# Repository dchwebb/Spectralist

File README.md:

# Spectralist

## Overview

Spectralist is an additive oscillator for Eurorack modular synthesisers. Up to 300 harmonics are output over two separate Odd and Even channels with a 'filter' offering a range of options for sculpting the harmonic spectrum of the output signals.

There are two harmonic modes - individual harmonics and sinusoidal waves of harmonics. In individual harmonic mode the spread controls adjust the spacing of the harmonics and the warp control either progressively bunches up or spreads out the harmonics. In the sinusoidal mode the spread controls increase the frequency of the 'waves' of harmonics.

The filter can be selected as a low pass filter with continuously adjustable slope or as a comb filter with adjustable tooth width and spread. In the comb filter mode the channel filter controls set the width between teeth and the slope sets the rise and fall times of the teeth. The individual channel filters controls can be adjusted with potentiometers or by CV with with trimmers to attenuate.

The pan CV input allows each channel to be smoothly panned between the two outputs. This can be used to mix the signals together in a mono setup, or used to dynamically shift the harmonics in the stereo field.

In the centre of the module is a ring of LEDs that give a visual representation of the harmonic spread and warp settings.

The module was designed in conjunction with musician Tal Shoshani who produced the following demonstration video:

## Technical

The module is based around an STM32H723VGT microcontroller, clocked at 400MHz. A TI PCM5100APW 32 bit audio DAC is used for the two channel outputs.

A TL072 dual op-amps is used to amplify and filter the DAC output (and/or phase invert) the outputs from 3V to 9V peak-to-peak at maximum. Input CV signals are conditioned by MCP6004 op-amps.

A USB B micro port is available at the rear of the unit for software updgrades and configuration via a serial connection.

The animated 25 LED display is driven over I2C by a PCA9956B LED Driver and the SMD LEDs sit on a daughter board raising them to the level of the front panel.

[Components schematic](Hardware/Spectralist_Components.pdf)

[LED daughterboard schematic](Hardware/Spectralist_LED_Daughterboard.pdf)

[Controls schematic](Hardware/Spectralist_Controls.pdf)

## Power

Analog power is supplied via a 3.3V LDO regulator and digital power uses a TPS561201 switching power supply.

- +12V current draw: 139 mA
- -12V Current draw: 7 mA

## Errata

Panel Errata: Mode switch hole too large for subminiature switch
Filter type switch hole just too narrow
Harm_Warp_pot and Harm_Stretch_Pot wrong way round (fixed 1.1)

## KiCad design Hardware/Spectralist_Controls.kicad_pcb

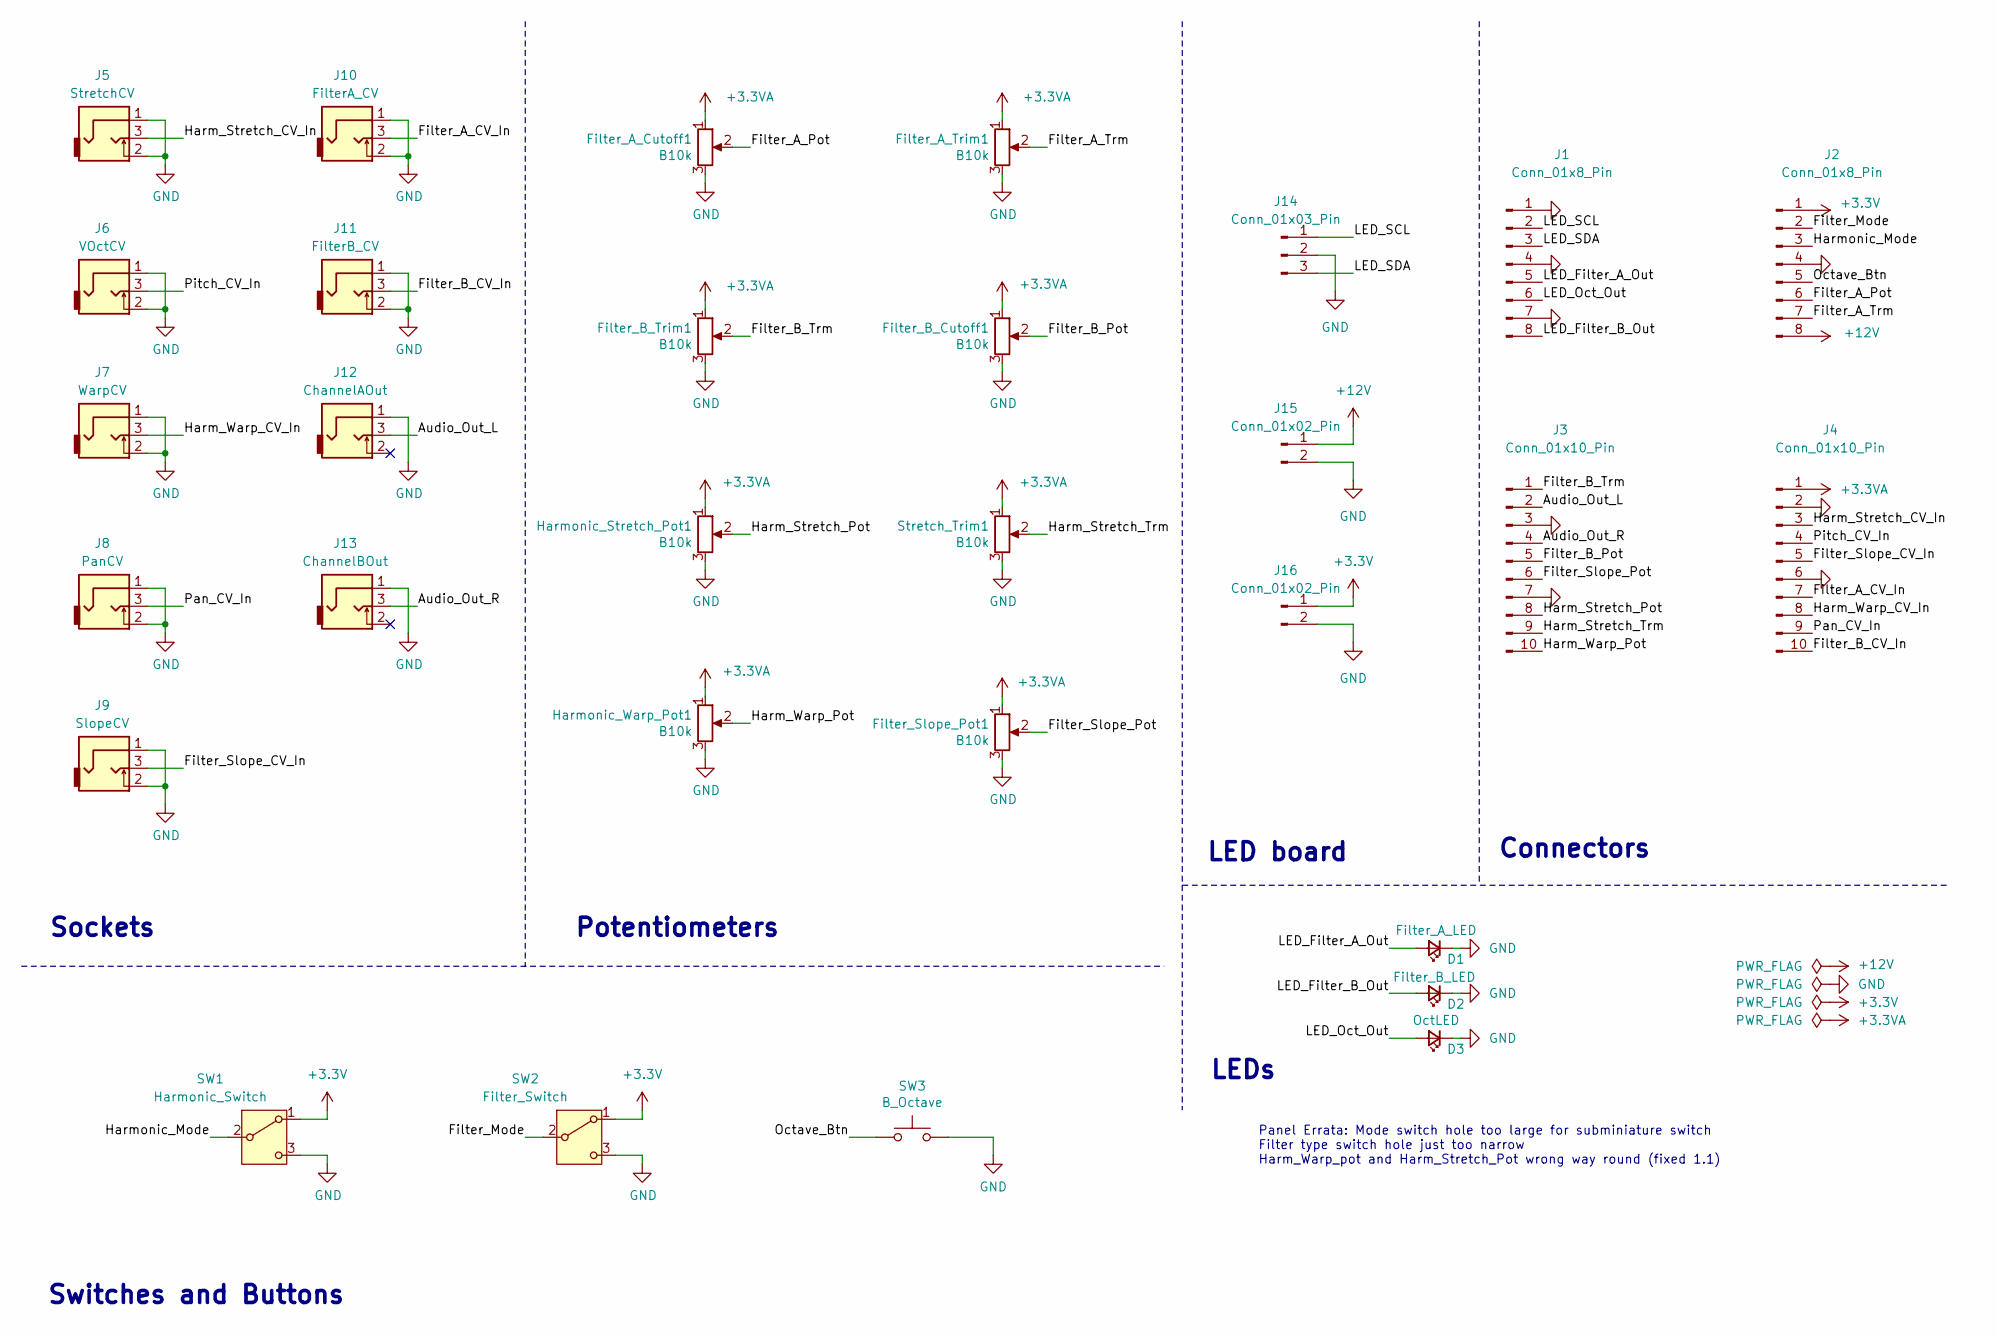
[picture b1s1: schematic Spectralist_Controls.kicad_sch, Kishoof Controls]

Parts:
D1: Filter_A_LED; LED_D3.0mm
D2: Filter_B_LED; LED_D3.0mm
D3: OctLED; LED_D3.0mm
Filter_A_Cutoff1: B10k; Alpha_9mm_Potentiometer_Aligned
Filter_A_Trim1: B10k; Alpha_9mm_Potentiometer_Aligned
Filter_B_Cutoff1: B10k; Alpha_9mm_Potentiometer_Aligned
Filter_B_Trim1: B10k; Alpha_9mm_Potentiometer_Aligned
Filter_Slope_Pot1: B10k; Alpha_9mm_Potentiometer_Aligned
Harmonic_Stretch_Pot1: B10k; Alpha_9mm_Potentiometer_Aligned
Harmonic_Warp_Pot1: B10k; Alpha_9mm_Potentiometer_Aligned
J1, J2: Conn_01x8_Pin; PinSocket_1x08_P2.54mm_Vertical
J3, J4: Conn_01x10_Pin; PinSocket_1x10_P2.54mm_Vertical
J5: StretchCV; THONKICONN_hole
J6: VOctCV; THONKICONN_hole
J7: WarpCV; THONKICONN_hole
J8: PanCV; THONKICONN_hole
J9: SlopeCV; THONKICONN_hole
J10: FilterA_CV; THONKICONN_hole
J11: FilterB_CV; THONKICONN_hole
J12: ChannelAOut; THONKICONN_hole
J13: ChannelBOut; THONKICONN_hole
J14: Conn_01x03_Pin; PinHeader_1x03_P2.54mm_Vertical
J15, J16: Conn_01x02_Pin; PinHeader_1x02_P2.54mm_Vertical
SW1: Harmonic_Switch; SPDT_SubMiniature_Aligned
SW2: Filter_Switch; SPDT_Miniature
SW3: B_Octave; SW_PUSH_6mm_aligned
Stretch_Trim1: B10k; Alpha_9mm_Potentiometer_Aligned

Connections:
+3.3V: J2.1, J16.1, SW1.1 (A), SW2.1 (A)
+3.3VA: Filter_A_Cutoff1.1, Filter_A_Trim1.1, Filter_B_Cutoff1.1, Filter_B_Trim1.1, Filter_Slope_Pot1.1, Harmonic_Stretch_Pot1.1, Harmonic_Warp_Pot1.1, J4.1, Stretch_Trim1.1
+12V: J2.8, J15.1
/Audio_Out_L: J3.2, J12.3
/Audio_Out_R: J3.4, J13.3
/Filter_A_CV_In: J4.7, J10.3
/Filter_A_Pot: Filter_A_Cutoff1.2, J2.6
/Filter_A_Trm: Filter_A_Trim1.2, J2.7
/Filter_B_CV_In: J4.10, J11.3
/Filter_B_Pot: Filter_B_Cutoff1.2, J3.5
/Filter_B_Trm: Filter_B_Trim1.2, J3.1
/Filter_Mode: J2.2, SW2.2 (B)
/Filter_Slope_CV_In: J4.5, J9.3
/Filter_Slope_Pot: Filter_Slope_Pot1.2, J3.6
/Harm_Stretch_CV_In: J4.3, J5.3
/Harm_Stretch_Pot: Harmonic_Stretch_Pot1.2, J3.8
/Harm_Stretch_Trm: J3.9, Stretch_Trim1.2
/Harm_Warp_CV_In: J4.8, J7.3
/Harm_Warp_Pot: Harmonic_Warp_Pot1.2, J3.10
/Harmonic_Mode: J2.3, SW1.2 (B)
/LED_Filter_A_Out: D1.2 (A), J1.5
/LED_Filter_B_Out: D2.2 (A), J1.8
/LED_Oct_Out: D3.2 (A), J1.6
/LED_SCL: J1.2, J14.1
/LED_SDA: J1.3, J14.3
/Octave_Btn: J2.5, SW3.1
/Pan_CV_In: J4.9, J8.3
/Pitch_CV_In: J4.4, J6.3
GND: D1.1 (K), D2.1 (K), D3.1 (K), Filter_A_Cutoff1.3, Filter_A_Trim1.3, Filter_B_Cutoff1.3, Filter_B_Trim1.3, Filter_Slope_Pot1.3, Harmonic_Stretch_Pot1.3, Harmonic_Warp_Pot1.3, J1.1, J1.4, J1.7, J2.4, J3.3, J3.7, J4.2, J4.6, J5.1, J5.2, J6.1, J6.2, J7.1, J7.2, J8.1, J8.2, J9.1, J9.2, J10.1, J10.2, J11.1, J11.2, J12.1, J13.1, J14.2, J15.2, J16.2, SW1.3 (C), SW2.3 (C), SW3.2, Stretch_Trim1.3

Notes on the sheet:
Sockets
Switches and Buttons
Panel Errata: Mode switch hole too large for subminiature switch Filter type switch hole just too narrow Harm_Warp_pot and Harm_Stretch_Pot wrong way round (fixed 1.1)
Connectors
LED board
LEDs
Potentiometers

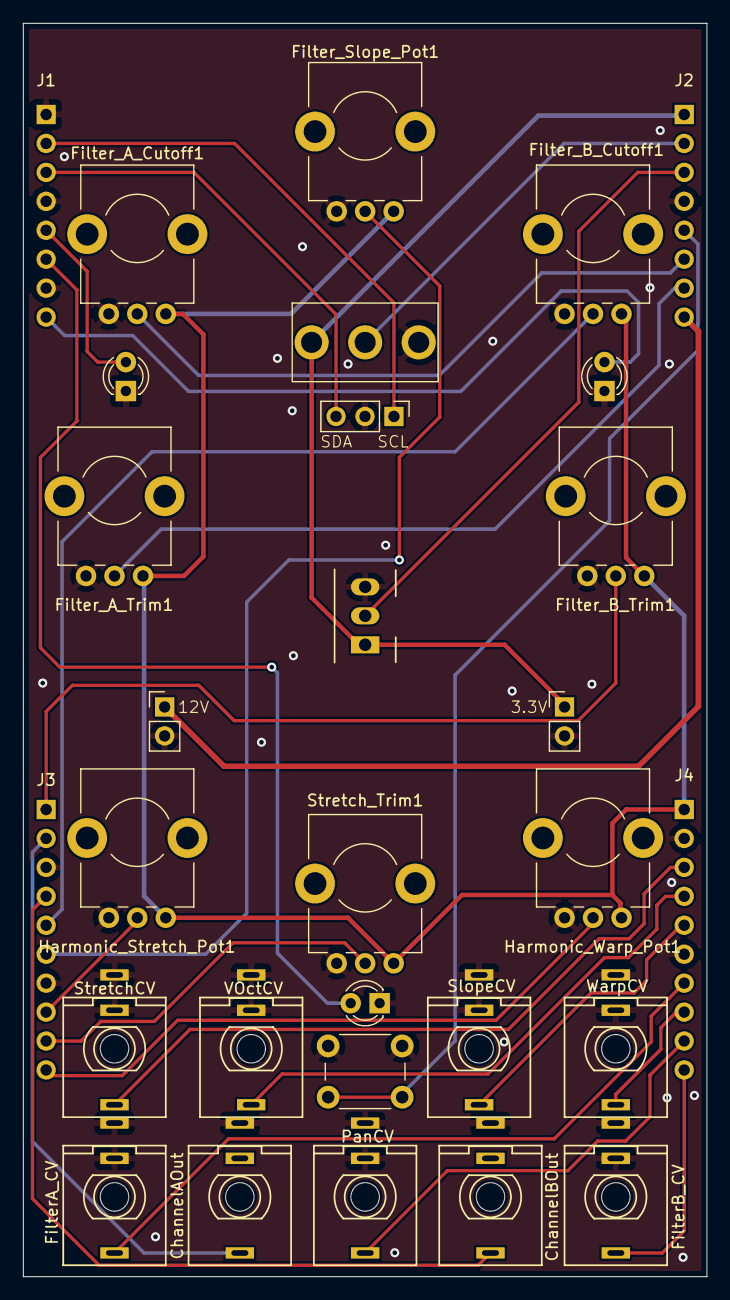
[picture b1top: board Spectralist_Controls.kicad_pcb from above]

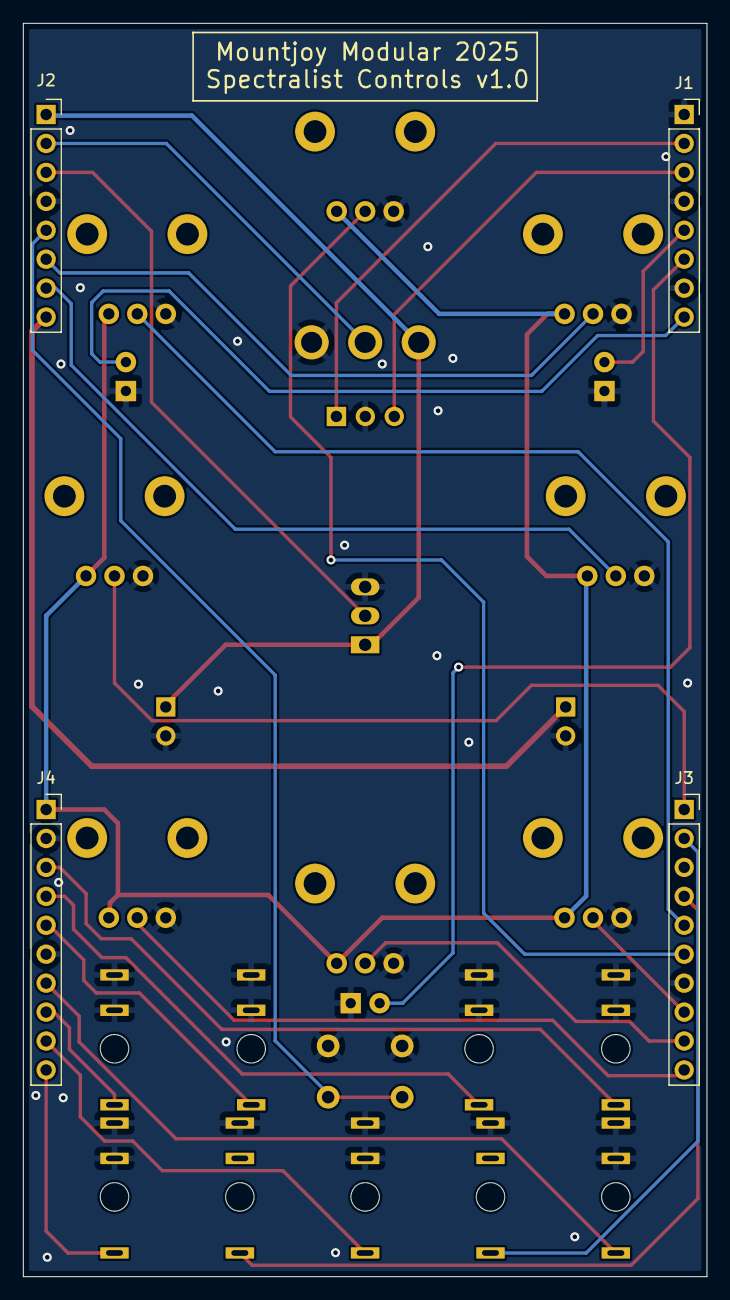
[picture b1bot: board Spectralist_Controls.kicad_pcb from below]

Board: 2 copper layers, 60.0 x 110.0 mm, 30 parts (4 on the bottom side), 29 nets.

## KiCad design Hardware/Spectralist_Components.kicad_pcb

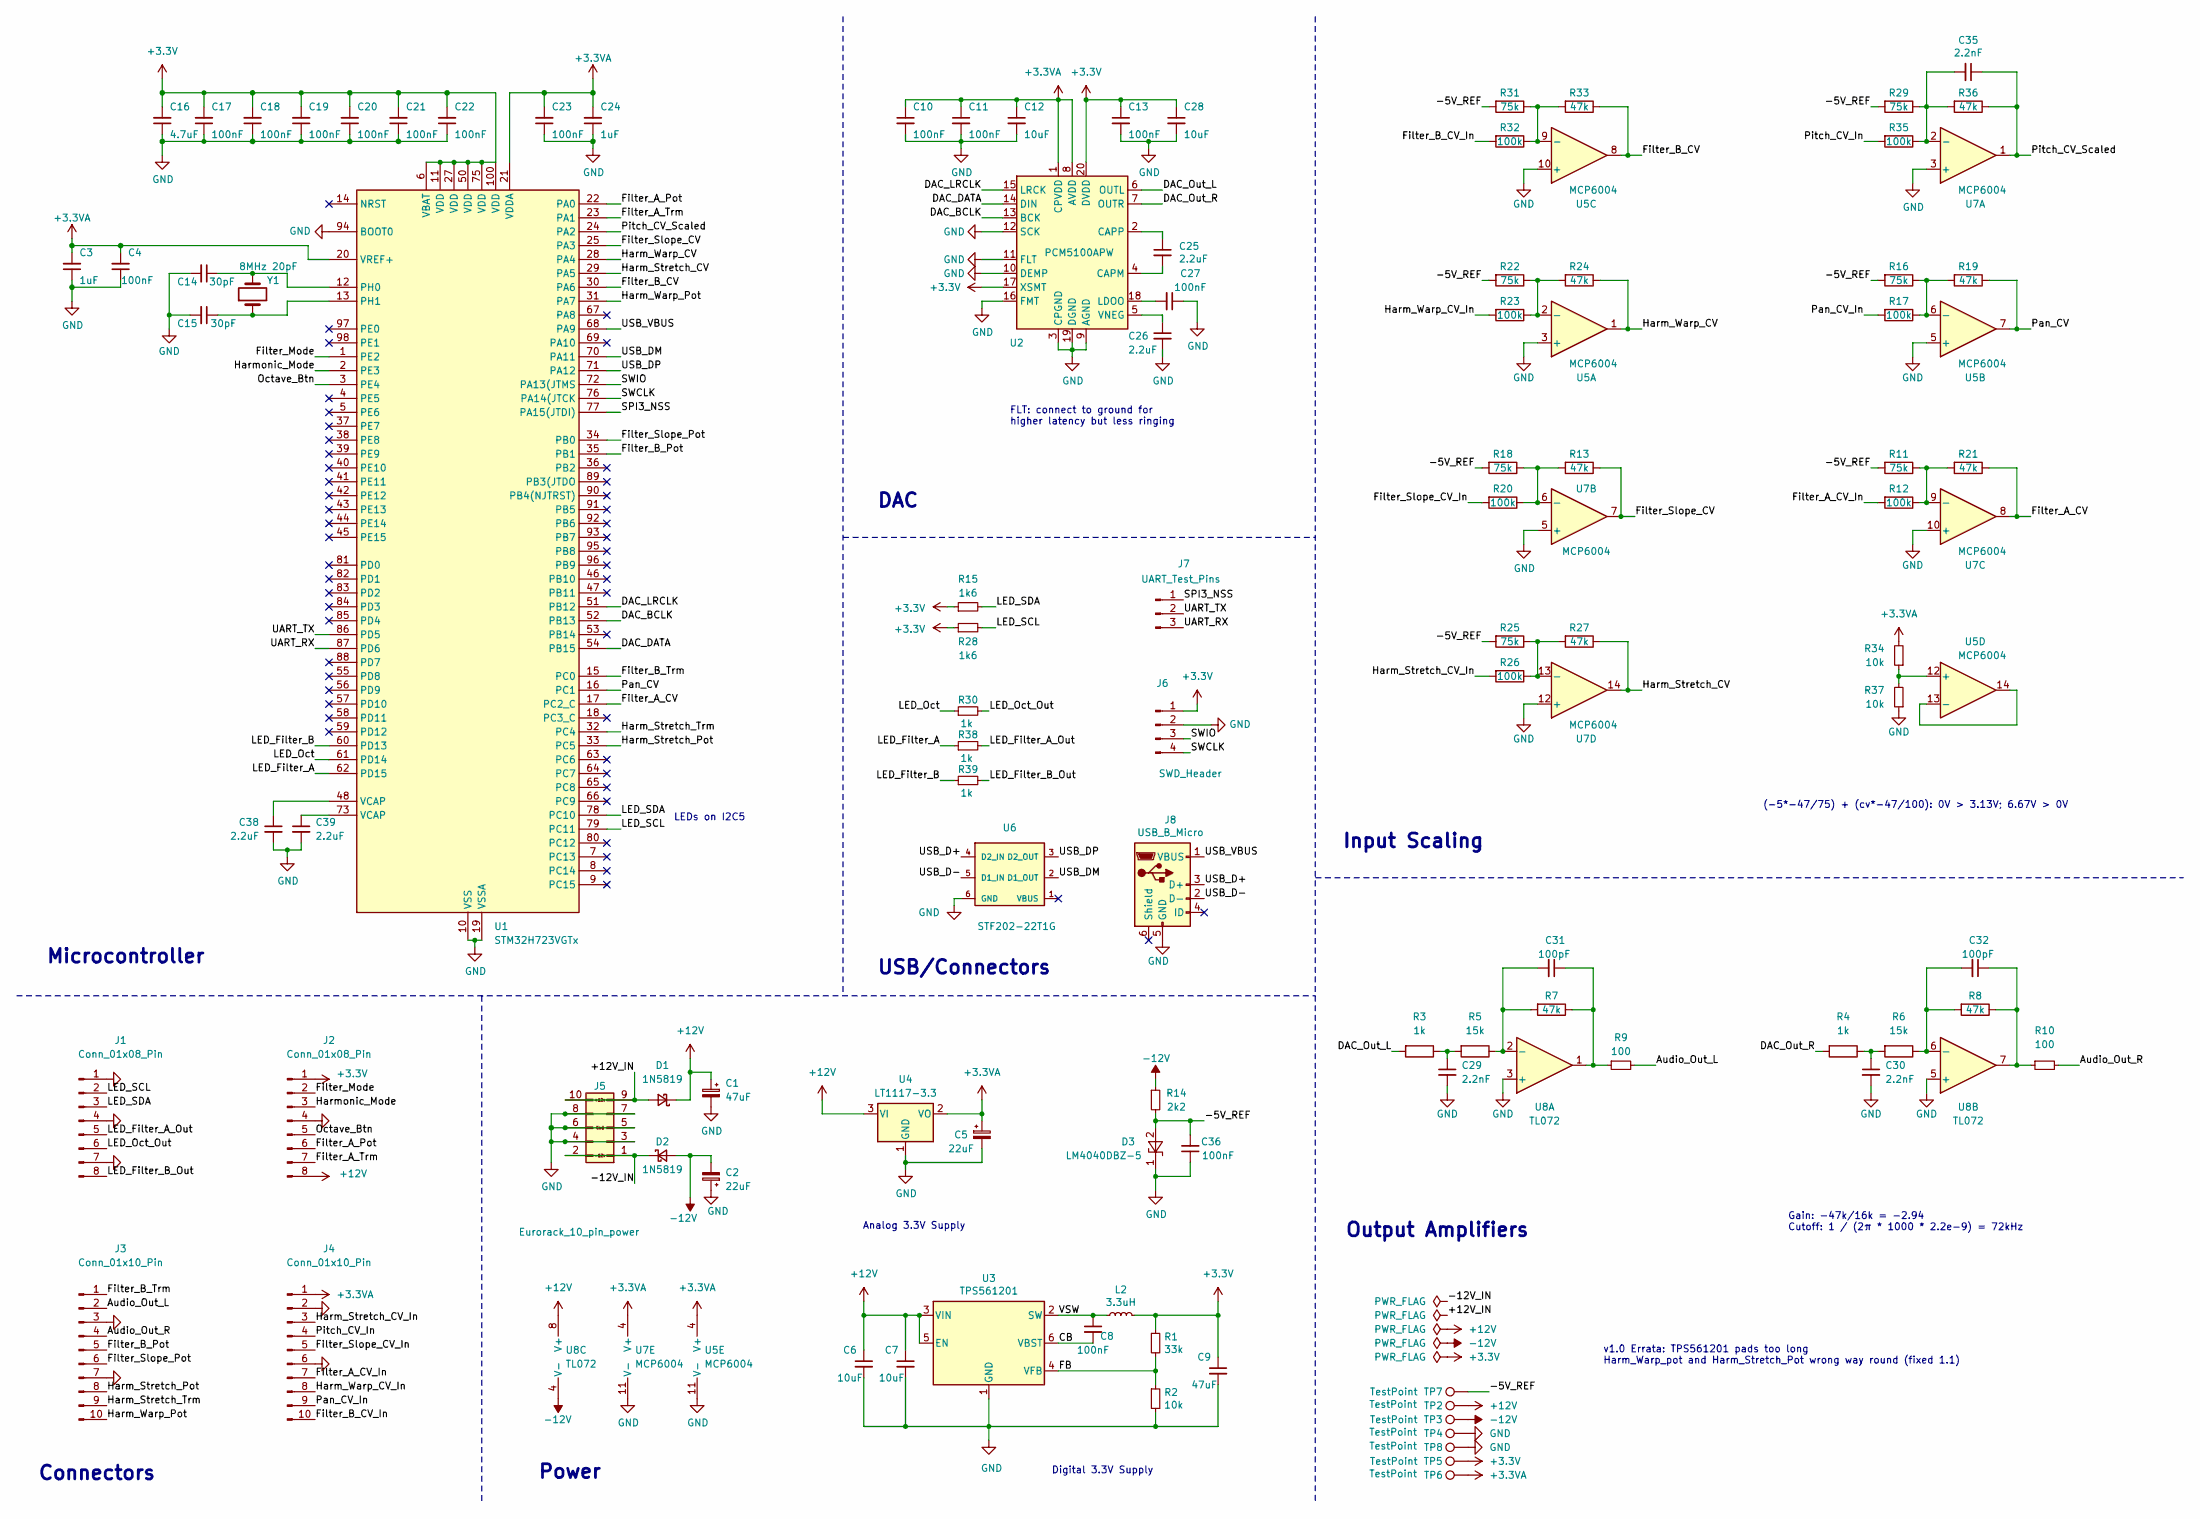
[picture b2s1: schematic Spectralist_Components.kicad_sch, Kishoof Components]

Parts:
C1: 47uF; CP_Elec_4x5.8
C2: 22uF; CP_Elec_4x5.8
C3, C24: 1uF; C_0603_1608Metric; Part_Number C15849
C4, C8, C10, C11, C13, C17, C18, C19, C20, C21, C22, C27, C36: 100nF; C_0603_1608Metric; Part_Number C14663
C5: 22uF; CP_Elec_4x5.8; Part_Number C134793
C6, C7: 10uF; C_0805_2012Metric; Part_Number C57112
C9: 47uF; C_1206_3216Metric; Part_Number C57112
C12, C28: 10uF; C_0603_1608Metric; Part_Number C15850
C14, C15: 30pF; C_0603_1608Metric; Part_Number C22397
C16: 4.7uF; C_0603_1608Metric; Part_Number C19666
C23: 100nF; C_0603_1608Metric; Part_Number C57112
C25, C26, C38, C39: 2.2uF; C_0603_1608Metric; Part_Number C23630
C29, C30, C35: 2.2nF; C_0603_1608Metric; Part_Number C1604
C31, C32: 100pF; C_0603_1608Metric; Part_Number C14858
D1, D2: 1N5819; D_SOD-123; Part_Number C8598
D3: LM4040DBZ-5; SOT-23; Part_Number C156291
J1, J2: Conn_01x08_Pin; PinHeader_1x08_P2.54mm_Vertical
J3, J4: Conn_01x10_Pin; PinHeader_1x10_P2.54mm_Vertical
J5: Eurorack_10_pin_power; Eurorack_10_pin_header
J6: SWD_Header; SWD_header
J7: UART_Test_Pins; PinHeader_1x03_P2.54mm_Vertical
J8: USB_B_Micro; USB_Micro-B_Amphenol
L2: 3.3uH; L_0806
R1: 33k; R_0603_1608Metric; Part_Number C25819
R2: 10k; R_0603_1608Metric; Part_Number C25804
R3, R4, R30, R38, R39: 1k; R_0603_1608Metric; Part_Number C4190
R5, R6: 15k; R_0603_1608Metric; Part_Number C25804
R7, R8, R13, R19, R21, R24, R27, R33, R36: 47k; R_0603_1608Metric; Part_Number C25819
R9, R10: 100; R_0603_1608Metric; Part_Number C4190
R11, R16, R18, R22, R25, R29, R31: 75k; R_0603_1608Metric; Part_Number C23242
R12, R17, R20, R23, R26, R32, R35: 100k; R_0603_1608Metric; Part_Number C23265
R14: 2k2; R_0603_1608Metric; Part_Number C4190
R15, R28: 1k6; R_0603_1608Metric; Part_Number C4190
R34, R37: 10k; R_0603_1608Metric; Part_Number C23162
TP2, TP3, TP4, TP5, TP6, TP7, TP8: TestPoint; 1.3mm_Test_Point
U1: STM32H723VGTx; LQFP-100_14x14mm_P0.5mm
U2: PCM5100APW; TSSOP-20_4.4x6.5mm_P0.65mm
U3: TPS561201; TSOT-23-6_HandSoldering
U4: LT1117-3.3; SOT-223-3_TabPin2
U5, U7: MCP6004; SO-14_3.9x8.65mm_P1.27mm
U6: STF202-22T1G
U8: TL072; SOIC-8_3.9x4.9mm_P1.27mm; Part_Number C6961
Y1: 8MHz 20pF; Crystal_SMD_Abracon_ABM3-2Pin_5.0x3.2mm; Part_Number C115962

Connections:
+3.3V: C9.1, C13.1, C16.2, C17.2, C18.2, C19.2, C20.2, C21.2, C22.2, C28.1, J2.1, J6.1, L2.2, R1.1, R15.1, R28.1, TP5.1, U1.6 (VBAT), U1.11 (VDD), U1.27 (VDD), U1.50 (VDD), U1.75 (VDD), U1.100 (VDD), U2.17 (XSMT), U2.20 (DVDD)
+3.3VA: C3.2, C4.2, C5.1, C10.1, C11.1, C12.1, C23.2, C24.2, J4.1, R34.2, TP6.1, U1.20 (VREF+), U1.21 (VDDA), U2.1 (CPVDD), U2.8 (AVDD), U4.2 (VO), U5.4 (V+), U7.4 (V+)
+12V: C1.1, C6.1, C7.1, D1.1 (K), J2.8, TP2.1, U3.3 (VIN), U3.5 (EN), U4.3 (VI), U8.8 (V+)
-12V: C2.2, D2.2 (A), R14.1, TP3.1, U8.4 (V-)
/+12V_IN: D1.2 (A), J5.9, J5.10
/-5V_REF: C36.2, D3.2 (A), R11.2, R14.2, R16.2, R18.2, R22.2, R25.2, R29.2, R31.2, TP7.1
/-12V_IN: D2.1 (K), J5.1, J5.2
/Audio_Out_L: J3.2, R9.2
/Audio_Out_R: J3.4, R10.2
/CB: C8.2, U3.6 (VBST)
/DAC_BCLK: U1.52 (PB13), U2.13 (BCK)
/DAC_DATA: U1.54 (PB15), U2.14 (DIN)
/DAC_LRCLK: U1.51 (PB12), U2.15 (LRCK)
/DAC_Out_L: R3.2, U2.6 (OUTL)
/DAC_Out_R: R4.2, U2.7 (OUTR)
/FB: R1.2, R2.1, U3.4 (VFB)
/Filter_A_CV: R21.1, U1.17 (PC2_C), U7.8
/Filter_A_CV_In: J4.7, R12.2
/Filter_A_Pot: J2.6, U1.22 (PA0)
/Filter_A_Trm: J2.7, U1.23 (PA1)
/Filter_B_CV: R33.1, U1.30 (PA6), U5.8
/Filter_B_CV_In: J4.10, R32.2
/Filter_B_Pot: J3.5, U1.35 (PB1)
/Filter_B_Trm: J3.1, U1.15 (PC0)
/Filter_Mode: J2.2, U1.1 (PE2)
/Filter_Slope_CV: R13.1, U1.25 (PA3), U7.7
/Filter_Slope_CV_In: J4.5, R20.2
/Filter_Slope_Pot: J3.6, U1.34 (PB0)
/Harm_Stretch_CV: R27.1, U1.29 (PA5), U7.14
/Harm_Stretch_CV_In: J4.3, R26.2
/Harm_Stretch_Pot: J3.8, U1.33 (PC5)
/Harm_Stretch_Trm: J3.9, U1.32 (PC4)
/Harm_Warp_CV: R24.1, U1.28 (PA4), U5.1
/Harm_Warp_CV_In: J4.8, R23.2
/Harm_Warp_Pot: J3.10, U1.31 (PA7)
/Harmonic_Mode: J2.3, U1.2 (PE3)
/LED_Filter_A: R38.1, U1.62 (PD15)
/LED_Filter_A_Out: J1.5, R38.2
/LED_Filter_B: R39.1, U1.60 (PD13)
/LED_Filter_B_Out: J1.8, R39.2
/LED_Oct: R30.1, U1.61 (PD14)
/LED_Oct_Out: J1.6, R30.2
/LED_SCL: J1.2, R28.2, U1.79 (PC11)
/LED_SDA: J1.3, R15.2, U1.78 (PC10)
/Octave_Btn: J2.5, U1.3 (PE4)
/Pan_CV: R19.1, U1.16 (PC1), U5.7
/Pan_CV_In: J4.9, R17.2
/Pitch_CV_In: J4.4, R35.2
/Pitch_CV_Scaled: C35.1, R36.1, U1.24 (PA2), U7.1
/SPI3_NSS: J7.1, U1.77 (PA15(JTDI))
/SWCLK: J6.4, U1.76 (PA14(JTCK)
/SWIO: J6.3, U1.72 (PA13(JTMS)
/UART_RX: J7.3, U1.87 (PD6)
/UART_TX: J7.2, U1.86 (PD5)
/USB_D+: J8.3 (D+), U6.4 (D2_IN)
/USB_D-: J8.2 (D-), U6.5 (D1_IN)
/USB_DM: U1.70 (PA11), U6.2 (D1_OUT)
/USB_DP: U1.71 (PA12), U6.3 (D2_OUT)
/USB_VBUS: J8.1 (VBUS), U1.68 (PA9)
/VSW: C8.1, L2.1, U3.2 (SW)
GND: C1.2, C2.1, C3.1, C4.1, C5.2, C6.2, C7.2, C9.2, C10.2, C11.2, C12.2, C13.2, C14.2, C15.2, C16.1, C17.1, C18.1, C19.1, C20.1, C21.1, C22.1, C23.1, C24.1, C26.2, C27.1, C28.2, C29.2, C30.2, C36.1, C38.2, C39.2, D3.1 (K), J1.1, J1.4, J1.7, J2.4, J3.3, J3.7, J4.2, J4.6, J5.3, J5.4, J5.5, J5.6, J5.7, J5.8, J6.2, J8.5 (GND), R2.2, R37.1, TP4.1, TP8.1, U1.10 (VSS), U1.19 (VSSA), U1.26 (VSS), U1.49 (VSS), U1.74 (VSS), U1.94 (BOOT0), U1.99 (VSS), U2.3 (CPGND), U2.9 (AGND), U2.10 (DEMP), U2.11 (FLT), U2.12 (SCK), U2.16 (FMT), U2.19 (DGND), U3.1 (GND), U4.1 (GND), U5.3 (+), U5.5 (+), U5.10 (+), U5.11 (V-), U6.6 (GND), U7.3 (+), U7.5 (+), U7.10 (+), U7.11 (V-), U7.12 (+), U8.3 (+), U8.5 (+)
unnamed: C29.1, R3.1, R5.2
unnamed: C30.1, R4.1, R6.2
unnamed: C31.1, R7.1, R9.1, U8.1
unnamed: C32.1, R8.1, R10.1, U8.7
unnamed: C38.1, U1.48 (VCAP)
unnamed: C39.1, U1.73 (VCAP)
unnamed: C14.1, U1.12 (PH0), Y1.2
unnamed: C15.1, U1.13 (PH1), Y1.1
unnamed: C25.2, U2.4 (CAPM)
unnamed: C25.1, U2.2 (CAPP)
unnamed: C27.2, U2.18 (LDOO)
unnamed: C26.1, U2.5 (VNEG)
unnamed: R22.1, R23.1, R24.2, U5.2 (-)
unnamed: R16.1, R17.1, R19.2, U5.6 (-)
unnamed: R31.1, R32.1, R33.2, U5.9 (-)
unnamed: R34.1, R37.2, U5.12 (+)
unnamed: U5.13 (-), U5.14
unnamed: C35.2, R29.1, R35.1, R36.2, U7.2 (-)
unnamed: R13.2, R18.1, R20.1, U7.6 (-)
unnamed: R11.1, R12.1, R21.2, U7.9 (-)
unnamed: R25.1, R26.1, R27.2, U7.13 (-)
unnamed: C31.2, R5.1, R7.2, U8.2 (-)
unnamed: C32.2, R6.1, R8.2, U8.6 (-)

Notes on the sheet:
DAC
Gain: -47k/16k = -2.94 Cutoff: 1 / (2π * 1000 * 2.2e-9) = 72kHz
Connectors
FLT: connect to ground for higher latency but less ringing
Digital 3.3V Supply
USB/Connectors
LEDs on I2C5
(-5*-47/75) + (cv*-47/100): 0V > 3.13V; 6.67V > 0V
v1.0 Errata: TPS561201 pads too long Harm_Warp_pot and Harm_Stretch_Pot wrong way round (fixed 1.1)
Input Scaling
Output Amplifiers
Power
Analog 3.3V Supply
Microcontroller

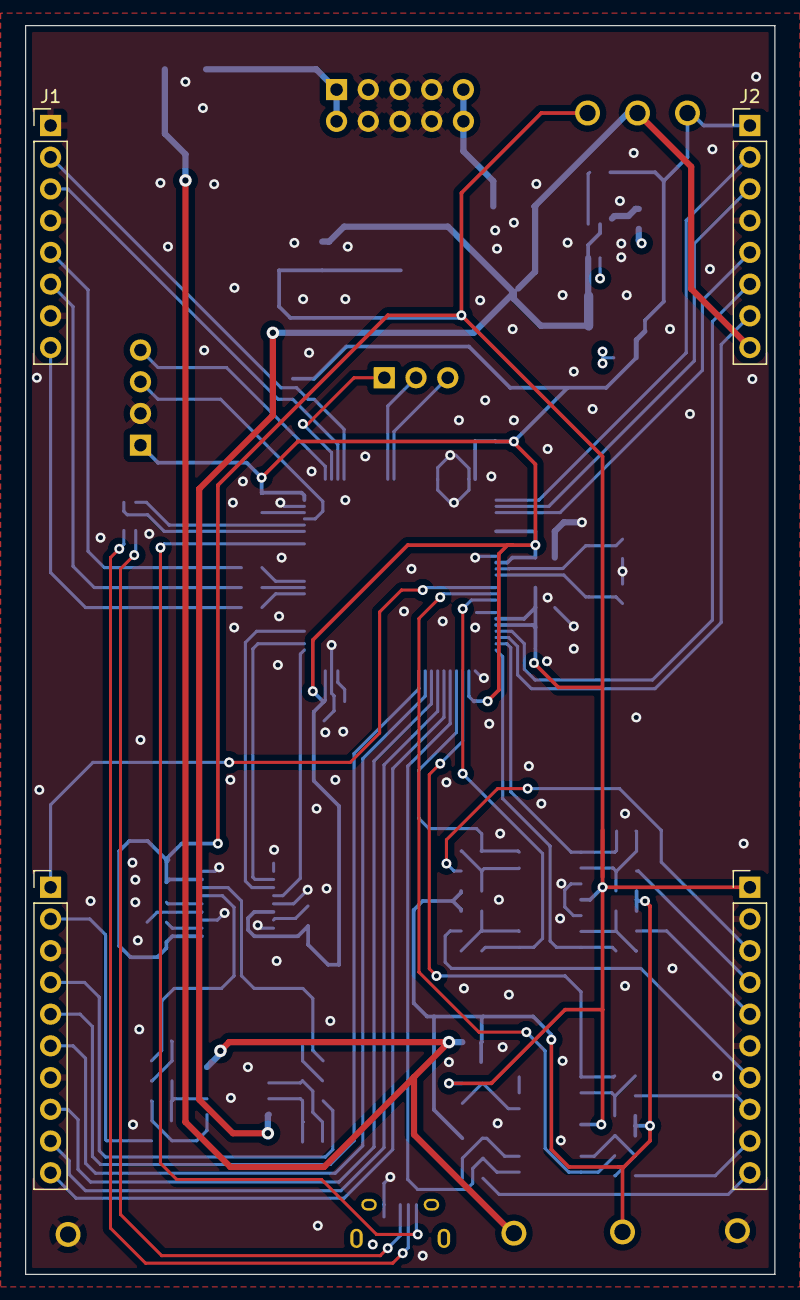
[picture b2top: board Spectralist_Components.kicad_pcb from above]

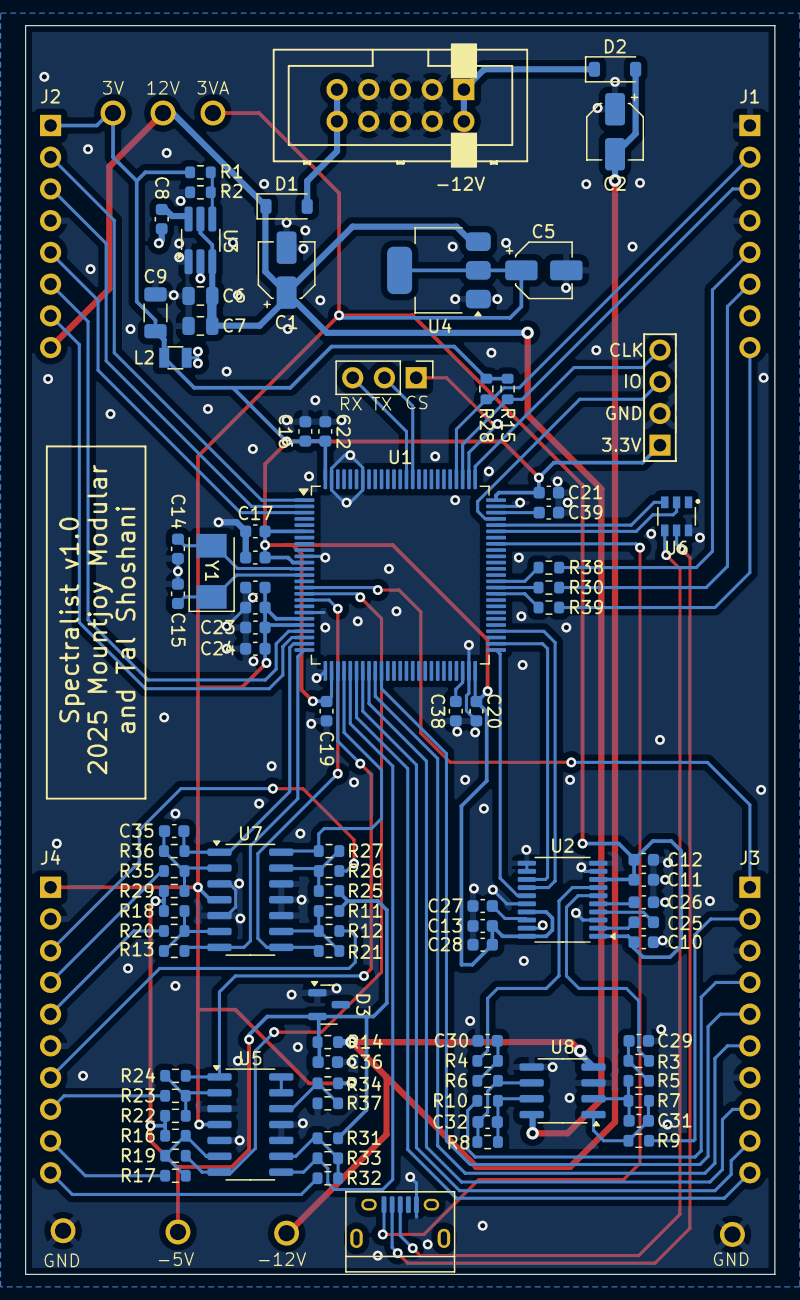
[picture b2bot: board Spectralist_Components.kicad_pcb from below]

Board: 4 copper layers, 60.0 x 100.0 mm, 103 parts (99 on the bottom side), 84 nets.

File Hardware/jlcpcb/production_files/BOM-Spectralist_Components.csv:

Comment,Designator,Footprint,LCSC
8MHz 20pF,Y1,Crystal_SMD_Abracon_ABM3-2Pin_5.0x3.2mm,C115962
PCM5100APW,U2,TSSOP-20_4.4x6.5mm_P0.65mm,C131154
100nF,"C10,C11,C13,C17,C18,C19,C20,C21,C22,C23,C27,C36,C4,C8",C_0603_1608Metric,C14663
100pF,"C31,C32",C_0603_1608Metric,C14858
1uF,"C24,C3",C_0603_1608Metric,C15849
2.2nF,"C29,C30,C35",C_0603_1608Metric,C1604
30pF,"C14,C15",C_0603_1608Metric,C1658
4.7uF,C16,C_0603_1608Metric,C19666
10uF,"C12,C28",C_0603_1608Metric,C19702
1k,"R3,R30,R38,R39,R4",R_0603_1608Metric,C21190
100,"R10,R9",R_0603_1608Metric,C22775
15k,"R5,R6",R_0603_1608Metric,C22809
1k6,"R15,R28",R_0603_1608Metric,C22843
75k,"R11,R16,R18,R22,R25,R29,R31",R_0603_1608Metric,C23242
2.2uF,"C25,C26,C38,C39",C_0603_1608Metric,C23630
100k,"R12,R17,R20,R23,R26,R32,R35",R_0603_1608Metric,C25803
10k,"R2,R34,R37",R_0603_1608Metric,C25804
47k,"R13,R19,R21,R24,R27,R33,R36,R7,R8",R_0603_1608Metric,C25819
2k2,R14,R_0603_1608Metric,C4190
33k,R1,R_0603_1608Metric,C4216
10uF,"C6,C7",C_0805_2012Metric,C440198
LT1117-3.3,U4,SOT-223-3_TabPin2,C6186
TL072,U8,SOIC-8_3.9x4.9mm_P1.27mm,C6961
STM32H723VGTx,U1,LQFP-100_14x14mm_P0.5mm,C730142
1N5819,"D1,D2",D_SOD-123,C8598
47uF,C9,C_1206_3216Metric,C96123

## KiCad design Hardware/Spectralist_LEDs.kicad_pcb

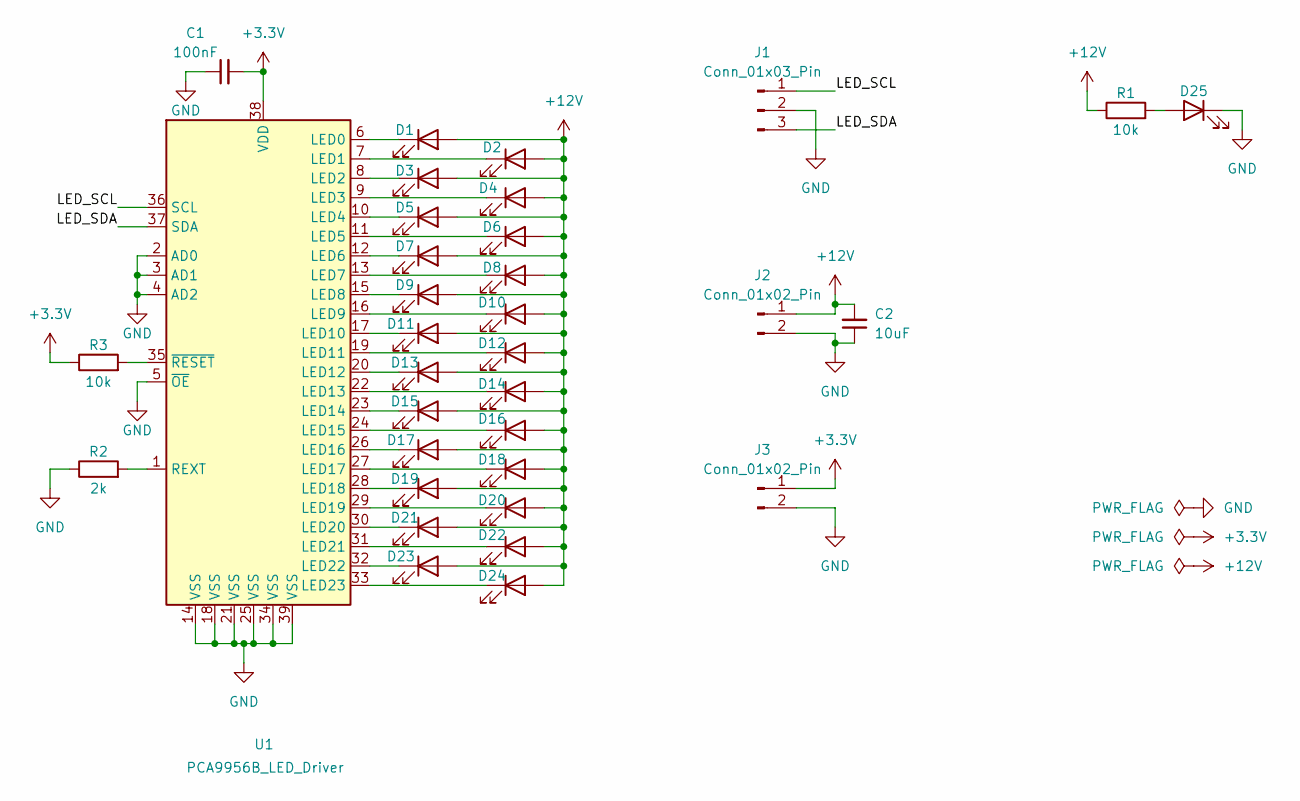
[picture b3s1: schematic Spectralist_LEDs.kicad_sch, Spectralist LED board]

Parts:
C1: 100nF; C_0603_1608Metric; Part_Number C14663
C2: 10uF; C_0805_2012Metric; Part_Number C14663
D1, D2, D3, D4, D5, D6, D7, D8, D9, D10, D11, D12, D13, D14, D15, D16, D17, D18, D19, D20, D21, D22, D23, D24, D25: LED; LED_0603_1608Metric
J1: Conn_01x03_Pin; PinHeader_1x03_P2.54mm_Vertical
J2, J3: Conn_01x02_Pin; PinHeader_1x02_P2.54mm_Vertical
R1, R3: 10k; R_0603_1608Metric
R2: 2k; R_0603_1608Metric
U1: PCA9956B_LED_Driver; HTSSOP-38_4.4x9.7mm_P0.5mm

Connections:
+3.3V: C1.2, J3.1, R3.1, U1.38 (VDD)
+12V: C2.2, D1.2 (A), D2.2 (A), D3.2 (A), D4.2 (A), D5.2 (A), D6.2 (A), D7.2 (A), D8.2 (A), D9.2 (A), D10.2 (A), D11.2 (A), D12.2 (A), D13.2 (A), D14.2 (A), D15.2 (A), D16.2 (A), D17.2 (A), D18.2 (A), D19.2 (A), D20.2 (A), D21.2 (A), D22.2 (A), D23.2 (A), D24.2 (A), J2.1, R1.1
/LED_SCL: J1.1, U1.36 (SCL)
/LED_SDA: J1.3, U1.37 (SDA)
GND: C1.1, C2.1, D25.1 (K), J1.2, J2.2, J3.2, R2.1, U1.2 (AD0), U1.3 (AD1), U1.4 (AD2), U1.5 (~OE), U1.14 (VSS), U1.18 (VSS), U1.21 (VSS), U1.25 (VSS), U1.34 (VSS), U1.39 (VSS)
unnamed: D1.1 (K), U1.6 (LED0)
unnamed: D2.1 (K), U1.7 (LED1)
unnamed: D3.1 (K), U1.8 (LED2)
unnamed: D4.1 (K), U1.9 (LED3)
unnamed: D5.1 (K), U1.10 (LED4)
unnamed: D6.1 (K), U1.11 (LED5)
unnamed: D7.1 (K), U1.12 (LED6)
unnamed: D8.1 (K), U1.13 (LED7)
unnamed: D9.1 (K), U1.15 (LED8)
unnamed: D10.1 (K), U1.16 (LED9)
unnamed: D11.1 (K), U1.17 (LED10)
unnamed: D12.1 (K), U1.19 (LED11)
unnamed: D13.1 (K), U1.20 (LED12)
unnamed: D14.1 (K), U1.22 (LED13)
unnamed: D15.1 (K), U1.23 (LED14)
unnamed: D16.1 (K), U1.24 (LED15)
unnamed: D17.1 (K), U1.26 (LED16)
unnamed: D18.1 (K), U1.27 (LED17)
unnamed: D19.1 (K), U1.28 (LED18)
unnamed: D20.1 (K), U1.29 (LED19)
unnamed: D21.1 (K), U1.30 (LED20)
unnamed: D22.1 (K), U1.31 (LED21)
unnamed: D23.1 (K), U1.32 (LED22)
unnamed: D24.1 (K), U1.33 (LED23)
unnamed: D25.2 (A), R1.2
unnamed: R2.2, U1.1 (REXT)
unnamed: R3.2, U1.35 (~RESET)

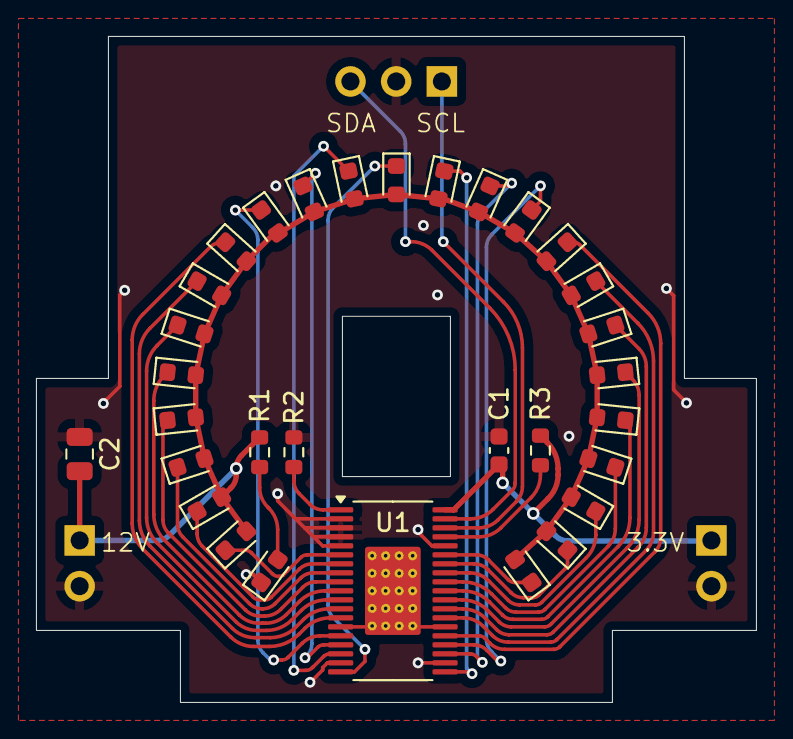
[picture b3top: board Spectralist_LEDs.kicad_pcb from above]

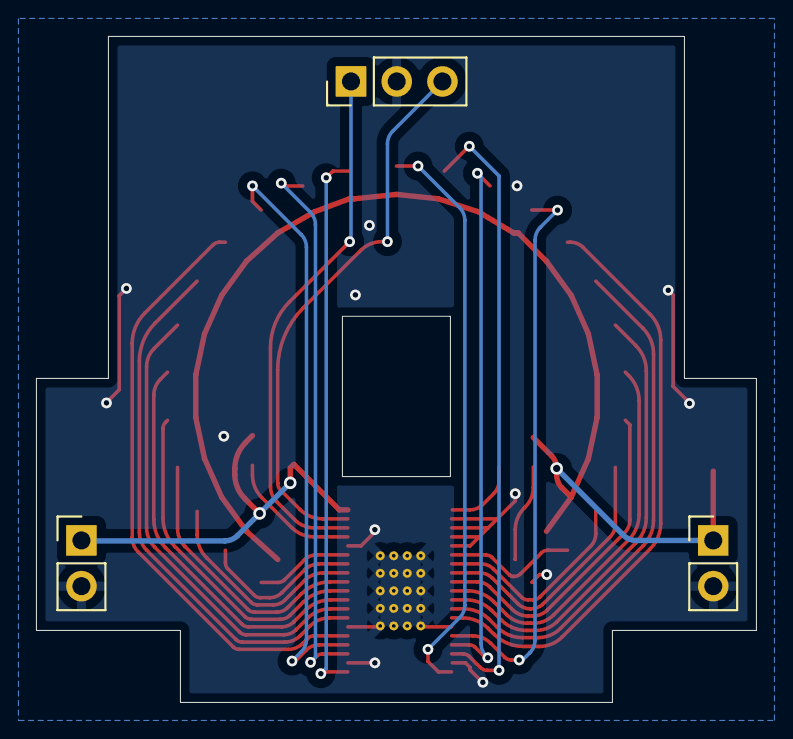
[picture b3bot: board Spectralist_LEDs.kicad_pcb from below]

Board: 2 copper layers, 40.0 x 37.0 mm, 34 parts (3 on the bottom side), 32 nets.

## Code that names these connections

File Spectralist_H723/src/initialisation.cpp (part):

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#include "Calib.h"
#include <cstring>

GpioPin debugPin1	{GPIOD, 6, GpioPin::Type::Output};			// PD5: Debug (also UART_TX)
GpioPin debugPin2	{GPIOD, 5, GpioPin::Type::Output};			// PD6: Debug (also UART_RX)
GpioPin debugPin3	{GPIOA, 15, GpioPin::Type::Output};			// PA15: Debug (also SPI_NSS)

// Clock overview:
// I2S 				PLL2 P 				61.44 MHz
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
/*-----------------------------------------------------------------------------------------------------------------
ADC1:
	PA0 ADC1_INP16 Filter_A_Pot
	PA1 ADC1_INP17 Filter_A_Trm
	PA2 ADC1_INP14 Pitch_CV_Scaled
	PA3 ADC1_INP15 Filter_Slope_CV
	PA4 ADC1_INP18 Harm_Warp_CV
	PA5 ADC1_INP19 Harm_Stretch_CV
ADC2:
	PA6 ADC12_INP3 Filter_B_CV
	PA7 ADC12_INP7 Harm_Stretch_Pot
	PB0 ADC12_INP9 Filter_Slope_Pot
	PB1 ADC12_INP5 Filter_B_Pot
	PC4 ADC12_INP4 Harm_Stretch_Trm
	PC5 ADC12_INP8 Harm_Warp_Pot
ADC3:
	PC0 ADC123_INP10 Filter_B_Trm
	PC1	ADC123_INP11 Pan_CV
	PC2_C ADC3_INP0 Filter_A_CV

*/

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
	/*--------------------------------------------------------------------------------------------
	Configure ADC Channels to be converted:
	PA0 ADC1_INP16 Filter_A_Pot
	PA1 ADC1_INP17 Filter_A_Trm
	PA2 ADC1_INP14 Pitch_CV_Scaled
	PA3 ADC1_INP15 Filter_Slope_CV
	PA4 ADC1_INP18 Harm_Warp_CV
	PA5 ADC1_INP19 Harm_Stretch_CV
	*/
	InitAdcPins(ADC1, {16, 17, 14, 15, 18, 19});

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	while ((ADC2->CR & ADC_CR_ADCAL) == ADC_CR_ADCAL) {};

	/* Configure ADC Channels to be converted:
	PA6 ADC12_INP3 Filter_B_CV
	PA7 ADC12_INP7 Harm_Warp_Pot
	PB0 ADC12_INP9 Filter_Slope_Pot
	PB1 ADC12_INP5 Filter_B_Pot
	PC4 ADC12_INP4 Harm_Stretch_Trm
	PC5 ADC12_INP8 Harm_Stretch_Pot
	*/
	InitAdcPins(ADC2, {3, 7, 9, 5, 4, 8});

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	while ((ADC3->CR & ADC_CR_ADCAL) == ADC_CR_ADCAL) {};

	/* Configure ADC Channels to be converted:
	PC0 ADC123_INP10 Filter_B_Trm
	PC1	ADC123_INP11 Pan_CV
	PC2_C ADC3_INP0 Filter_A_CV
	*/
	InitAdcPins(ADC3, {10, 11, 0});

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{
	RCC->APB1LENR |= RCC_APB1LENR_SPI2EN;			//	Enable SPI clocks

	GpioPin::Init(GPIOB, 12, GpioPin::Type::AlternateFunction, 5);		// PB12: I2S2_WS [alternate function AF5]
	GpioPin::Init(GPIOB, 13, GpioPin::Type::AlternateFunction, 5);		// PB13: I2S2_CK [alternate function AF5]
	GpioPin::Init(GPIOB, 15, GpioPin::Type::AlternateFunction, 5);		// PB15: I2S2_SDO [alternate function AF5]

	// Configure SPI (Shown as SPI2->CGFR in SFR)
	SPI2->I2SCFGR |= SPI_I2SCFGR_I2SMOD;			// I2S Mode
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
void InitPWMTimer()
{
	// PD13: TIM4_CH2 LED_Filter_B
	// PD15: TIM4_CH4 LED_Filter_A
	RCC->APB1LENR |= RCC_APB1LENR_TIM4EN;

	GpioPin::Init(GPIOD, 13, GpioPin::Type::AlternateFunction, 2);		// Enable channel 1 PWM output pin on PE2
	GpioPin::Init(GPIOD, 15, GpioPin::Type::AlternateFunction, 2);		// Enable channel 2 PWM output pin on PE3

	TIM4->CCMR1 |= TIM_CCMR1_OC2PE;					// Output compare 2 preload enable
	TIM4->CCMR2 |= TIM_CCMR2_OC4PE;					// Output compare 4 preload enable
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
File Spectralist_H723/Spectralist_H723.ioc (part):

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Mcu.Name=STM32H723VGTx
Mcu.Package=LQFP100
Mcu.UserName=STM32H723VGTx
PA0.Mode=IN16-Single-Ended
PA0.Signal=ADC1_INP16
PA1.Mode=IN17-Single-Ended
PA1.Signal=ADC1_INP17
PA11.Mode=Device_Only_FS
PA11.Signal=USB_OTG_HS_DM
PA12.Mode=Device_Only_FS
PA12.Signal=USB_OTG_HS_DP
PA13(JTMS/SWDIO).Mode=Serial_Wire
PA13(JTMS/SWDIO).Signal=DEBUG_JTMS-SWDIO
PA14(JTCK/SWCLK).Mode=Serial_Wire
PA14(JTCK/SWCLK).Signal=DEBUG_JTCK-SWCLK
PA15(JTDI).Signal=SPI3_NSS
PA2.Signal=ADCx_INP14
PA3.Signal=ADCx_INP15
PA4.Signal=ADCx_INP18
PA5.Signal=ADCx_INP19
PA6.Signal=ADCx_INP3
PA7.Signal=ADCx_INP7
PA9.Mode=Activate_VBUS_FS
PA9.Signal=USB_OTG_HS_VBUS
PB0.Signal=ADCx_INP9
PB1.Signal=ADCx_INP5
PB12.Mode=Half_Duplex_Master_Tx
PB12.Signal=I2S2_WS
PB13.Mode=Half_Duplex_Master_Tx
PB13.Signal=I2S2_CK
PB15.Mode=Half_Duplex_Master_Tx
PB15.Signal=I2S2_SDO
PC0.Signal=ADCx_INP10
PC1.Signal=ADCx_INP11
PC10.Mode=I2C
PC10.Signal=I2C5_SDA
PC11.Mode=I2C
PC11.Signal=I2C5_SCL
PC2_C.Mode=IN0-Single-Ended
PC2_C.Signal=ADC3_INP0
PC4.Signal=ADCx_INP4
PC5.Signal=ADCx_INP8
PD13.Signal=S_TIM4_CH2
PD14.GPIOParameters=GPIO_Label
PD14.GPIO_Label=Octave_LED_Output
PD14.Signal=GPIO_Output
PD15.Signal=S_TIM4_CH4
PD5.Mode=Asynchronous
PD5.Signal=USART2_TX
PD6.Mode=Asynchronous
PD6.Signal=USART2_RX
PE2.Signal=GPIO_Input
PE3.Signal=GPIO_Input
PE4.Signal=GPIO_Input
PH0-OSC_IN.Mode=HSE-External-Oscillator
PH0-OSC_IN.Signal=RCC_OSC_IN
PH1-OSC_OUT.Mode=HSE-External-Oscillator
PH1-OSC_OUT.Signal=RCC_OSC_OUT
RCC.HSE_VALUE=8000000
RCC.SYSCLKFreq_VALUE=400000000
RCC.SYSCLKSource=RCC_SYSCLKSOURCE_PLLCLK
board=custom
